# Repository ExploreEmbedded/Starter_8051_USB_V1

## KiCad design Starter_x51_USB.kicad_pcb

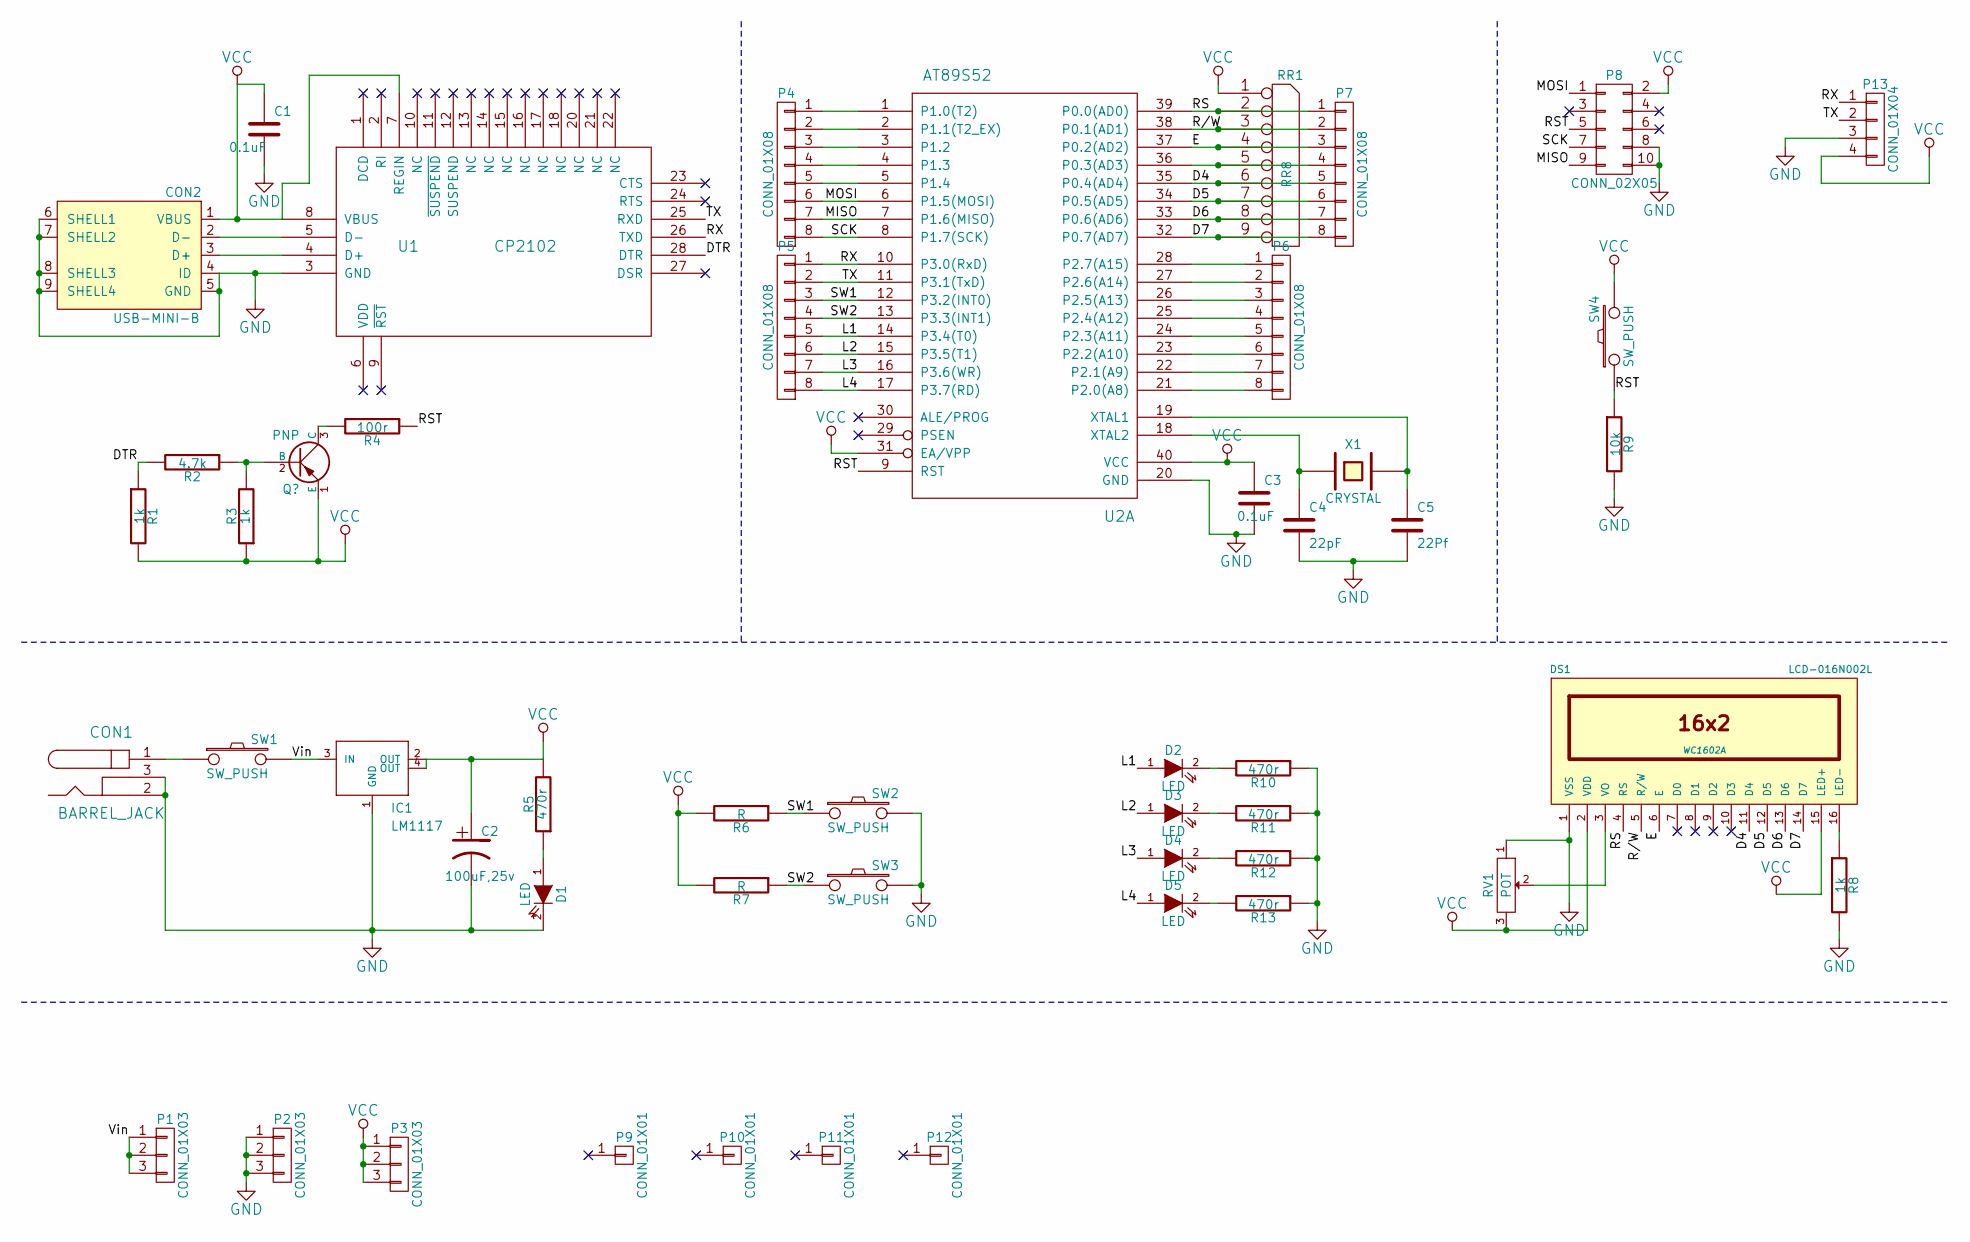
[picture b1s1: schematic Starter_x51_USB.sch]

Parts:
C1, C3: 0.1uF
C2: 100uF,25v
C4: 22pF
C5: 22Pf
CON1: BARREL_JACK
CON2: USB-MINI-B
D1, D2, D3, D4, D5: LED
DS1: LCD-016N002L; WC1602A
IC1: LM1117
P1, P2, P3: CONN_01X03
P4, P5, P6, P7: CONN_01X08
P8: CONN_02X05
P9, P10, P11, P12: CONN_01X01
P13: CONN_01X04
R1, R3, R8: 1k
R2: 4.7k
R4: 100r
R5, R10, R11, R12, R13: 470r
R6, R7: R
R9: 10k
RR1: RR8
RV1: POT
SW1, SW2, SW3, SW4: SW_PUSH
U1: CP2102
U2: AT89S52
X1: CRYSTAL

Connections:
/D4: DS1.11 (D4), P7.5, RR1.6, U2.35 (P0.4(AD4))
/D5: DS1.12 (D5), P7.6, RR1.7, U2.34 (P0.5(AD5))
/D6: DS1.13 (D6), P7.7, RR1.8, U2.33 (P0.6(AD6))
/D7: DS1.14 (D7), P7.8, RR1.9, U2.32 (P0.7(AD7))
/DTR: R1.1, R2.2, U1.28 (DTR)
/E: DS1.6 (E), P7.3, RR1.4, U2.37 (P0.2(AD2))
/L1: D2.1 (A), P5.5, U2.14 (P3.4(T0))
/L2: D3.1 (A), P5.6, U2.15 (P3.5(T1))
/L3: D4.1 (A), P5.7, U2.16 (P3.6(WR))
/L4: D5.1 (A), P5.8, U2.17 (P3.7(RD))
/MISO: P4.7, P8.9, U2.7 (P1.6(MISO))
/MOSI: P4.6, P8.1, U2.6 (P1.5(MOSI))
/R/W: DS1.5 (R/W), P7.2, RR1.3, U2.38 (P0.1(AD1))
/RS: DS1.4 (RS), P7.1, RR1.2, U2.39 (P0.0(AD0))
/RST: P8.5, R4.1, R9.1, SW4.1, U2.9 (RST)
/RX: P5.1, P13.1, U1.26 (TXD), U2.10 (P3.0(RxD))
/SCK: P4.8, P8.7, U2.8 (P1.7(SCK))
/SW1: P5.3, R6.1, SW2.1, U2.12 (P3.2(INT0))
/SW2: P5.4, R7.1, SW3.1, U2.13 (P3.3(INT1))
/TX: P5.2, P13.2, U1.25 (RXD), U2.11 (P3.1(TxD))
/Vin: IC1.3 (IN), P1.1, P1.2, P1.3, SW1.2
GND: C1.2, C2.2, C3.2, C4.2, C5.2, CON1.2, CON1.3, CON2.4 (ID), CON2.5 (GND), CON2.6 (SHELL1), CON2.7 (SHELL2), CON2.8 (SHELL3), CON2.9 (SHELL4), D1.2 (K), DS1.1 (VSS), IC1.1 (GND), P2.1, P2.2, P2.3, P8.8, P8.10, P13.3, R8.2, R9.2, R10.1, R11.1, R12.1, R13.1, RV1.1, SW2.2, SW3.2, U1.3 (GND), U2.20 (GND)
unnamed: C4.1, U2.18 (XTAL2), X1.1
unnamed: C5.1, U2.19 (XTAL1), X1.2
unnamed: CON1.1, SW1.1
unnamed: CON2.2 (D-), U1.5 (D-)
unnamed: CON2.3 (D+), U1.4 (D+)
unnamed: D1.1 (A), R5.1
unnamed: D2.2 (K), R10.2
unnamed: D3.2 (K), R11.2
unnamed: D4.2 (K), R12.2
unnamed: D5.2 (K), R13.2
unnamed: DS1.3 (VO), RV1.2
unnamed: DS1.16 (LED-), R8.1
unnamed: P4.1, U2.1 (P1.0(T2))
unnamed: P4.2, U2.2 (P1.1(T2_EX))
unnamed: P4.3, U2.3 (P1.2)
unnamed: P4.4, U2.4 (P1.3)
unnamed: P4.5, U2.5 (P1.4)
unnamed: P6.1, U2.28 (P2.7(A15))
unnamed: P6.2, U2.27 (P2.6(A14))
unnamed: P6.3, U2.26 (P2.5(A13))
unnamed: P6.4, U2.25 (P2.4(A12))
unnamed: P6.5, U2.24 (P2.3(A11))
unnamed: P6.6, U2.23 (P2.2(A10))
unnamed: P6.7, U2.22 (P2.1(A9))
unnamed: P6.8, U2.21 (P2.0(A8))
unnamed: P7.4, RR1.5, U2.36 (P0.3(AD3))
unnamed 59: R2.1, R3.2; also elsewhere on the board
unnamed 60: R4.2; also elsewhere on the board
VCC: C1.1, C2.1, C3.1, CON2.1 (VBUS), DS1.2 (VDD), DS1.15 (LED+), IC1.2 (OUT), IC1.4 (OUT), P3.1, P3.2, P3.3, P8.2, P13.4, R1.2, R3.1, R5.2, R6.2, R7.2, RR1.1 (COM), RV1.3, SW4.2, U1.7 (REGIN), U1.8 (VBUS), U2.31 (EA/VPP), U2.40 (VCC); also elsewhere on the board

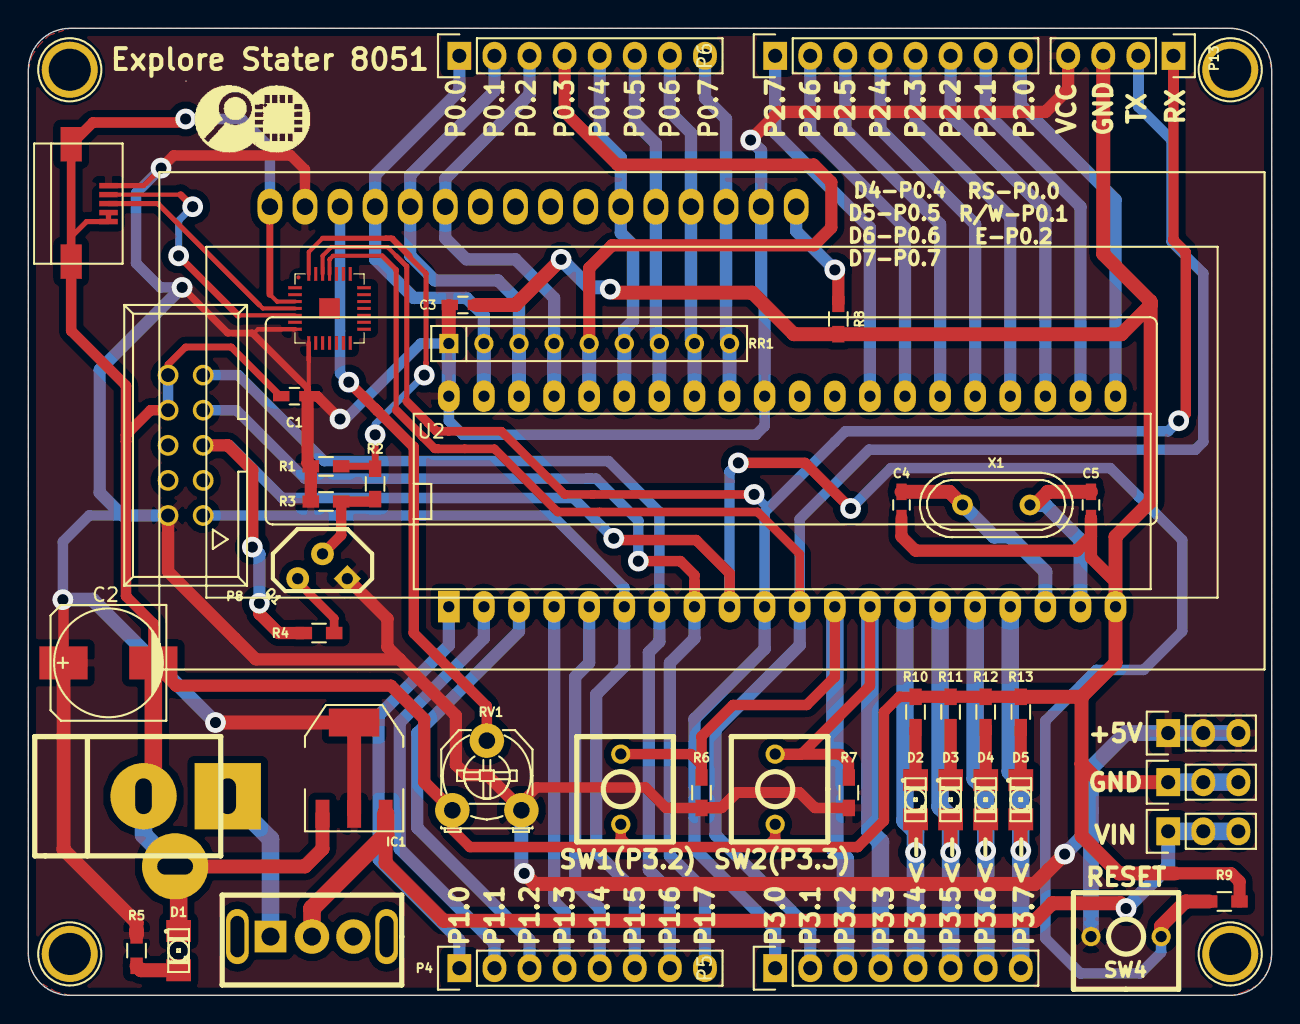
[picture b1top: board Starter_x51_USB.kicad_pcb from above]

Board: 2 copper layers, 90.0 x 70.0 mm, 52 parts (1 on the bottom side), 51 nets.

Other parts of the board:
LOGO: LOGO (1)
LOGO#2: LOGO (2)
Q1: PNP; BC557

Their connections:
unnamed 59: Q1.2; also elsewhere on the board
unnamed 60: Q1.3; also elsewhere on the board
VCC: Q1.1; also elsewhere on the board

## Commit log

2015-11-07 Added Fileas
2015-11-10 routing
2015-11-17 corrected files
2015-12-25 Final Design
